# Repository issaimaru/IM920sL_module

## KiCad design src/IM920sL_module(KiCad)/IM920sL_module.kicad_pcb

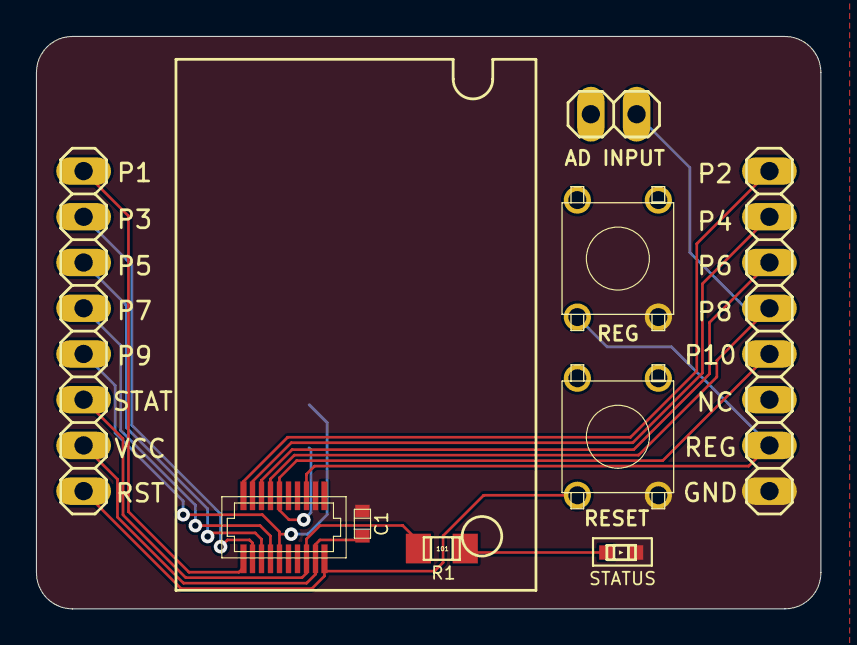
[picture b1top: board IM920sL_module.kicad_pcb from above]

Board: 2 copper layers, 43.6 x 31.8 mm, 11 parts (0 on the bottom side), 16 nets.

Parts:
AD_MODE1: PINHD-1X2; 1X02
C1: GCM188L81H104KA57
CN1: 20P5.0-JMCS-G-TF(N)
JP1, JP2: PINHD-1X8; 1X08
R1: RG2012N-101-B-T5; RG2012
R2, R3: RG2012-0Ω; RG2012
STATUS: SML-E12V8WT86
SW1, SW2: 一般的なタクトスイッチ

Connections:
/P1: CN1.IO1/BUSY, JP1.1
/P2: CN1.IO2, JP2.1
/P3: CN1.IO3, JP1.2
/P4: CN1.IO4, JP2.2
/P5: CN1.IO5, JP1.3
/P6: CN1.IO6/RXD, JP2.3
/P7: CN1.IO7/TXD, JP1.4
/P8: AD_MODE1.2, CN1.IO8, JP2.4
/P9: CN1.IO9, JP1.5, R2.LEFT
/P10: CN1.IO10, JP2.5, R3.LEFT
/REG: CN1.REG, JP2.7, SW1.REG
/RESET: CN1.RESET, JP1.8, SW2.RESET
/STATUS: CN1.STATUS, JP1.6, R1.RIGHT
/VCC: AD_MODE1.1, C1.P$1, CN1.VCC, JP1.7, R2.RIGHT, R3.RIGHT
GND: C1.P$2, CN1.GND, JP2.8, STATUS.K, SW1.T2, SW2.T2
unnamed: R1.LEFT, STATUS.A

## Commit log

2022-10-30 回路図の完成
2022-10-30 Eagle移行前_配線図完成
2022-10-31 基板デザイン完成_gerber出力後
2022-10-31 基板デザインの改良
2022-10-31 基板デザインの改良2
